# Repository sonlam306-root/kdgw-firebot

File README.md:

# kdgw-firebot — FireBot, robot chữa cháy chạy ray

FireBot là robot chữa cháy treo ngược dưới ray. Khi trạm gọi cháy phát hiện lửa, robot chạy tới vị trí, ngắm bằng camera nhiệt MLX90640 rồi phun nước qua tay 3 khớp. Trạm chính KD-GW vừa sạc pin vừa tiếp nước cho robot. Mọi nút điều khiển trong hệ đều dùng ESP.

| Hạng mục | Thông số |
|---|---|
| Ray | 2 tầng, nhôm dẹt 60×6 dựng đứng, dài 5 m hình chữ L, cua R600, mặt ray dưới cao 1,2 m so với sàn |
| Truyền động | Bánh xe chịu tải (vòng bi U626ZZ, trục M6 cấp 12.9); động cơ tuyến tính 12 V ở **cả 2 tầng ray**, chạy cùng pha (ADR-10) nên bình tự đẩy, robot không kéo bình; chia 9 module |
| Tốc độ | 1 m/s trên đoạn thẳng, 0,6 m/s khi vào cua |
| Phun | Tay 3 khớp, khớp 1 xoay 270° (DS3225 bản 270°): phun được **cả 2 bên ray**, bên nào có cháy thì phun bên đó (ADR-11) |
| Robot | Pin Li-ion 3S 12 V, bơm áp lực 12 V tầm phun 4–5 m, bình 3–4 L có cảm biến mực nước, phanh lò xo tự đóng khi mất điện |
| Điều khiển | KD-GW điều phối qua ESP-NOW và làm cầu sang MQTT; 2 trạm gọi cháy dùng ESP32-S3-CAM + cảm biến IR + nút nhấn |

## Thư mục

```
docs/                 bản vẽ tổng thể, catalog chi tiết in 3D, bản vẽ mạch in (PDF)
hardware/3d/          mô hình OpenSCAD tham số + STL (45 file) + ảnh render
hardware/pcb/FB-TRK/  board module ray ×9 (ESP32-C3, MAX3485, Hall, 2 driver DRV8313: ray dưới + ray trên)
hardware/pcb/FB-ROB/  board robot (ESP32-S3 DevKitC, 3 ngõ MOSFET, 4 servo, cảm biến)
firmware/             trk · rob · call · gw (chưa viết)
tools/                script sinh KiCad + autoroute (kigen), script vẽ PDF
```

## Tài liệu dự án
- SPEC (đã duyệt Checkpoint 1): https://claude.ai/artifact/Peooq6djiB6K9hsrVTQUn5
- PRODUCT (ADR-01…09): https://claude.ai/artifact/P67EzTibhUqXJA8hx2qiaA
- BOM dự toán: https://claude.ai/artifact/SVUP8KTw6aWDFcNGWLDG2Z (≈ 24,8 triệu đ, đã gồm 10 % dự phòng)

## Lắp đặt trạm gọi cháy
Mang đi triển lãm: dùng **khung định vị** (ADR-13, `hardware/3d/firebot_jig.scad`, STL ở `hardware/3d/stl_jig/`) — thanh sắt V lỗ bắt vào chân cột P2/P6, cột camera cắm đúng lỗ, chỉ hiệu chuẩn 1 lần ở nhà rồi chọn cấu hình trên dashboard.

Đo và dạy vị trí cho từng trạm theo `docs/Huong_dan_dat_tram_goi_chay.pdf` (ADR-12): dán thước số dọc ray, đo s_L, s_R bằng chân vuông góc, dạy trạm bằng ngọn nến, chạy thử không phun.

## Bước tiếp theo — thử nghiệm M0
1. Lắp 1 module ray + bogie dưới, đo lực đẩy (cần ≥ 5 N liên tục).
2. Thử bơm 12 V: đo tầm phun và lưu lượng.
3. Thử MLX90640 với bảng tra đạn đạo.

Board có chữ "Arden" ở mặt dưới.

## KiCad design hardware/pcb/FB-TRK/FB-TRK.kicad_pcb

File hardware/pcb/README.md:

# FireBot – mạch in (rev A, 2026-11-25)

| Board | Kích thước | SL | Gắn vào | File gửi xưởng |
|---|---|---|---|---|
| FB-TRK (module ray, 2 driver: ray dưới + ray trên) | 76 × 56 mm, 2 lớp | 9 (+1 dự phòng) | hộp `module_box`, 4 trụ M2.5 (64 × 44) | `FB-TRK/FB-TRK_gerber.zip` |
| FB-ROB (robot) | 84 × 84 mm, 2 lớp | 1 (+1 dự phòng) | khay `electronics_tray`, 4 trụ M3 (74 × 54) | `FB-ROB/FB-ROB_gerber.zip` |

- Mở bằng KiCad 7 trở lên: `*.kicad_pro`, sơ đồ `*.kicad_sch`, mạch `*.kicad_pcb`. Sơ đồ nối bằng nhãn net, chưa vẽ dây.
- Đặt hàng: FR4 1,6 mm. FB-ROB nên chọn đồng 2 oz vì đường bơm chịu ~5 A.
- Kiểm tra DRC: 0 lỗi, 0 chỗ chưa nối, ở cả hai board.
- Mỗi board có chữ "Arden" ở mặt dưới, góc phải. Không in tên board.
- Danh sách linh kiện: `*_bom.csv`. Toạ độ linh kiện cho SMT: `*_cpl.csv`.

**Kiểm tra trước khi hàn**
1. **ESP32-C3 SuperMini:** so chữ in trên PCB với chữ in trên module, vì vài lô xếp chân khác.
2. **ESP32-S3-DevKitC-1:** đo khoảng cách 2 hàng chân, bản vẽ dùng 22,86 mm.
3. **SimpleFOC Mini:** bản v1.0 và v1.1 xếp chân khác nhau, nên nối dây Dupont theo tên chân.

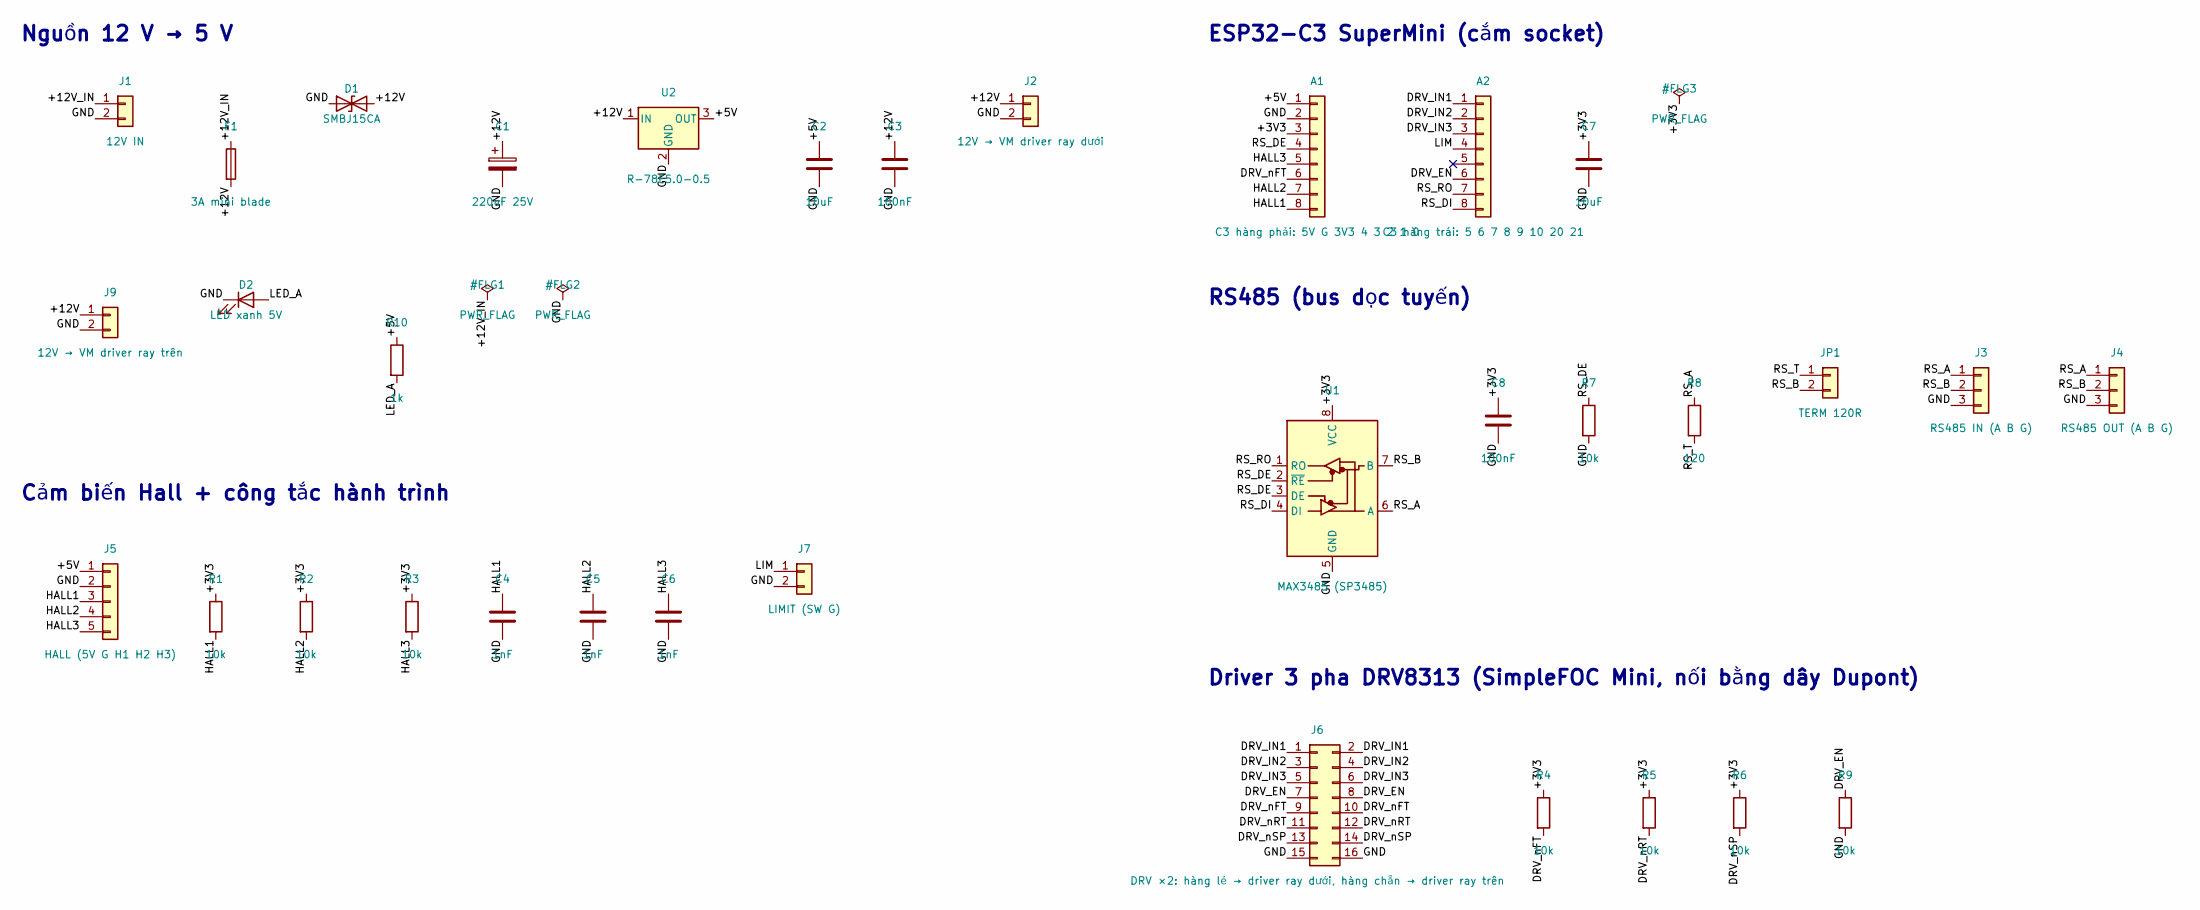
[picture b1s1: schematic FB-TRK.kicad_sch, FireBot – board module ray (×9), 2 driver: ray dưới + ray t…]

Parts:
A1: C3 hàng phải: 5V G 3V3 4 3 2 1 0; PinSocket_1x08_P2.54mm_Vertical
A2: C3 hàng trái: 5 6 7 8 9 10 20 21; PinSocket_1x08_P2.54mm_Vertical
C1: 220uF 25V; CP_Radial_D8.0mm_P3.50mm
C2, C7: 10uF; C_0805_2012Metric
C3, C8: 100nF; C_0805_2012Metric
C4, C5, C6: 1nF; C_0805_2012Metric
D1: SMBJ15CA; D_SMB
D2: LED xanh 5V; LED_0805_2012Metric
F1: 3A mini blade; Fuseholder_Blade_Mini_Keystone_3568
J1: 12V IN; TerminalBlock_Phoenix_MKDS-1,5-2-5.08_1x02_P5.08mm_Horizont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
J2: 12V → VM driver ray dưới; TerminalBlock_Phoenix_MKDS-1,5-2-5.08_1x02_P5.08mm_Horizont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
J3: RS485 IN (A B G); TerminalBlock_Phoenix_MKDS-1,5-3-5.08_1x03_P5.08mm_Horizont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
J4: RS485 OUT (A B G); TerminalBlock_Phoenix_MKDS-1,5-3-5.08_1x03_P5.08mm_Horizont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
J5: HALL (5V G H1 H2 H3); JST_XH_B5B-XH-A_1x05_P2.50mm_Vertical
J6: DRV ×2: hàng lẻ → driver ray dưới, hàng chẵn → dr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; PinHeader_2x08_P2.54mm_Vertical
J7: LIMIT (SW G); JST_XH_B2B-XH-A_1x02_P2.50mm_Vertical
J9: 12V → VM driver ray trên; TerminalBlock_Phoenix_MKDS-1,5-2-5.08_1x02_P5.08mm_Horizont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
JP1: TERM 120R; PinHeader_1x02_P2.54mm_Vertical
R1, R2, R3, R4, R5, R6, R7, R9: 10k; R_0805_2012Metric
R8: 120; R_0805_2012Metric
R10: 1k; R_0805_2012Metric
U1: MAX3485 (SP3485); SOIC-8_3.9x4.9mm_P1.27mm
U2: R-78E5.0-0.5; Converter_DCDC_RECOM_R-78E-0.5_THT

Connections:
+3V3: A1.3, C7.1, C8.1, R1.1, R2.1, R3.1, R4.1, R5.1, R6.1, U1.8 (VCC)
+5V: A1.1, C2.1, J5.1, R10.1, U2.3 (OUT)
+12V: C1.1, C3.1, D1.2 (A2), F1.2, J2.1, J9.1, U2.1 (IN)
+12V_IN: F1.1, J1.1
DRV_EN: A2.6, J6.7, J6.8, R9.1
DRV_IN1: A2.1, J6.1, J6.2
DRV_IN2: A2.2, J6.3, J6.4
DRV_IN3: A2.3, J6.5, J6.6
DRV_nFT: A1.6, J6.9, J6.10, R4.2
DRV_nRT: J6.11, J6.12, R5.2
DRV_nSP: J6.13, J6.14, R6.2
GND: A1.2, C1.2, C2.2, C3.2, C4.2, C5.2, C6.2, C7.2, C8.2, D1.1 (A1), D2.1 (K), J1.2, J2.2, J3.3, J4.3, J5.2, J6.15, J6.16, J7.2, J9.2, R7.2, R9.2, U1.5 (GND), U2.2 (GND)
HALL1: A1.8, C4.1, J5.3, R1.2
HALL2: A1.7, C5.1, J5.4, R2.2
HALL3: A1.5, C6.1, J5.5, R3.2
LED_A: D2.2 (A), R10.2
LIM: A2.4, J7.1
RS_A: J3.1, J4.1, R8.1, U1.6 (A)
RS_B: J3.2, J4.2, JP1.2, U1.7 (B)
RS_DE: A1.4, R7.1, U1.2 (~RE), U1.3 (DE)
RS_DI: A2.8, U1.4 (DI)
RS_RO: A2.7, U1.1 (RO)
RS_T: JP1.1, R8.2

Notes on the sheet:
Nguồn 12 V → 5 V
ESP32-C3 SuperMini (cắm socket)
RS485 (bus dọc tuyến)
Cảm biến Hall + công tắc hành trình
Driver 3 pha DRV8313 (SimpleFOC Mini, nối bằng dây Dupont)

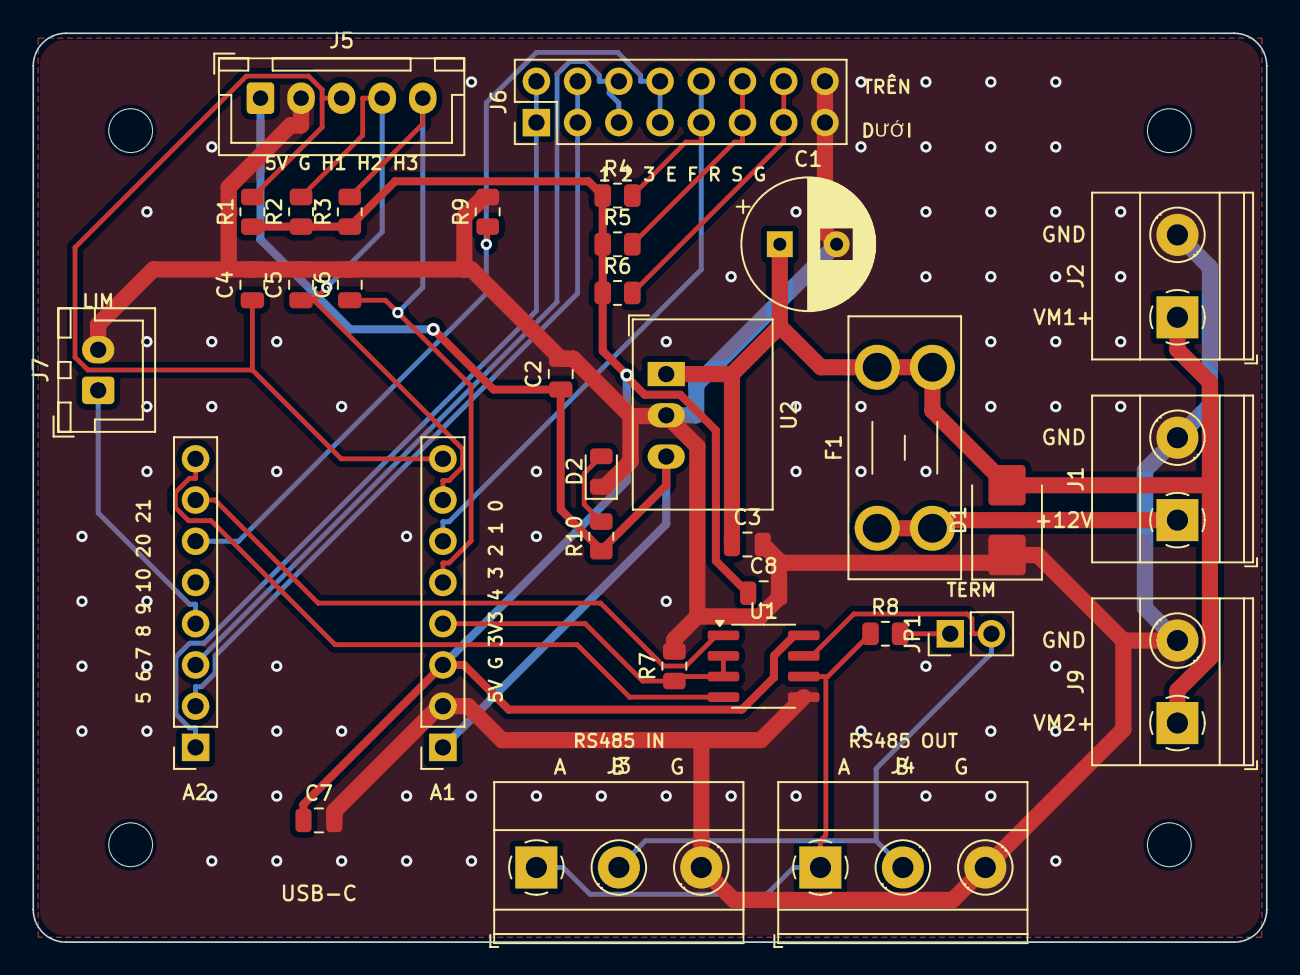
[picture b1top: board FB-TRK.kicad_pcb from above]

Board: 2 copper layers, 76.0 x 56.0 mm, 38 parts (0 on the bottom side), 23 nets.

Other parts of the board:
H1, H2, H3, H4: MountingHole_2.7mm_M2.5

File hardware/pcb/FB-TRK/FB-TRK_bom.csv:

Ref,Giá trị,Footprint,SL
A1,C3 hàng phải: 5V G 3V3 4 3 2 1 0,PinSocket_1x08_P2.54mm_Vertical,1
A2,C3 hàng trái: 5 6 7 8 9 10 20 21,PinSocket_1x08_P2.54mm_Vertical,1
C1,220uF 25V,CP_Radial_D8.0mm_P3.50mm,1
C2 C7,10uF,C_0805_2012Metric,2
C3 C8,100nF,C_0805_2012Metric,2
C4 C5 C6,1nF,C_0805_2012Metric,3
D1,SMBJ15CA,D_SMB,1
D2,LED xanh 5V,LED_0805_2012Metric,1
F1,3A mini blade,Fuseholder_Blade_Mini_Keystone_3568,1
J1,12V IN,"TerminalBlock_Phoenix_MKDS-1,5-2-5.08_1x02_P5.08mm_Horizontal",1
J2,12V → VM driver ray dưới,"TerminalBlock_Phoenix_MKDS-1,5-2-5.08_1x02_P5.08mm_Horizontal",1
J3,RS485 IN (A B G),"TerminalBlock_Phoenix_MKDS-1,5-3-5.08_1x03_P5.08mm_Horizontal",1
J4,RS485 OUT (A B G),"TerminalBlock_Phoenix_MKDS-1,5-3-5.08_1x03_P5.08mm_Horizontal",1
J5,HALL (5V G H1 H2 H3),JST_XH_B5B-XH-A_1x05_P2.50mm_Vertical,1
J6,"DRV ×2: hàng lẻ → driver ray dưới, hàng chẵn → driver ray trên",PinHeader_2x08_P2.54mm_Vertical,1
J7,LIMIT (SW G),JST_XH_B2B-XH-A_1x02_P2.50mm_Vertical,1
J9,12V → VM driver ray trên,"TerminalBlock_Phoenix_MKDS-1,5-2-5.08_1x02_P5.08mm_Horizontal",1
JP1,TERM 120R,PinHeader_1x02_P2.54mm_Vertical,1
R1 R2 R3 R4 R5 R6 R7 R9,10k,R_0805_2012Metric,8
R8,120,R_0805_2012Metric,1
R10,1k,R_0805_2012Metric,1
U1,MAX3485 (SP3485),SOIC-8_3.9x4.9mm_P1.27mm,1
U2,R-78E5.0-0.5,Converter_DCDC_RECOM_R-78E-0.5_THT,1

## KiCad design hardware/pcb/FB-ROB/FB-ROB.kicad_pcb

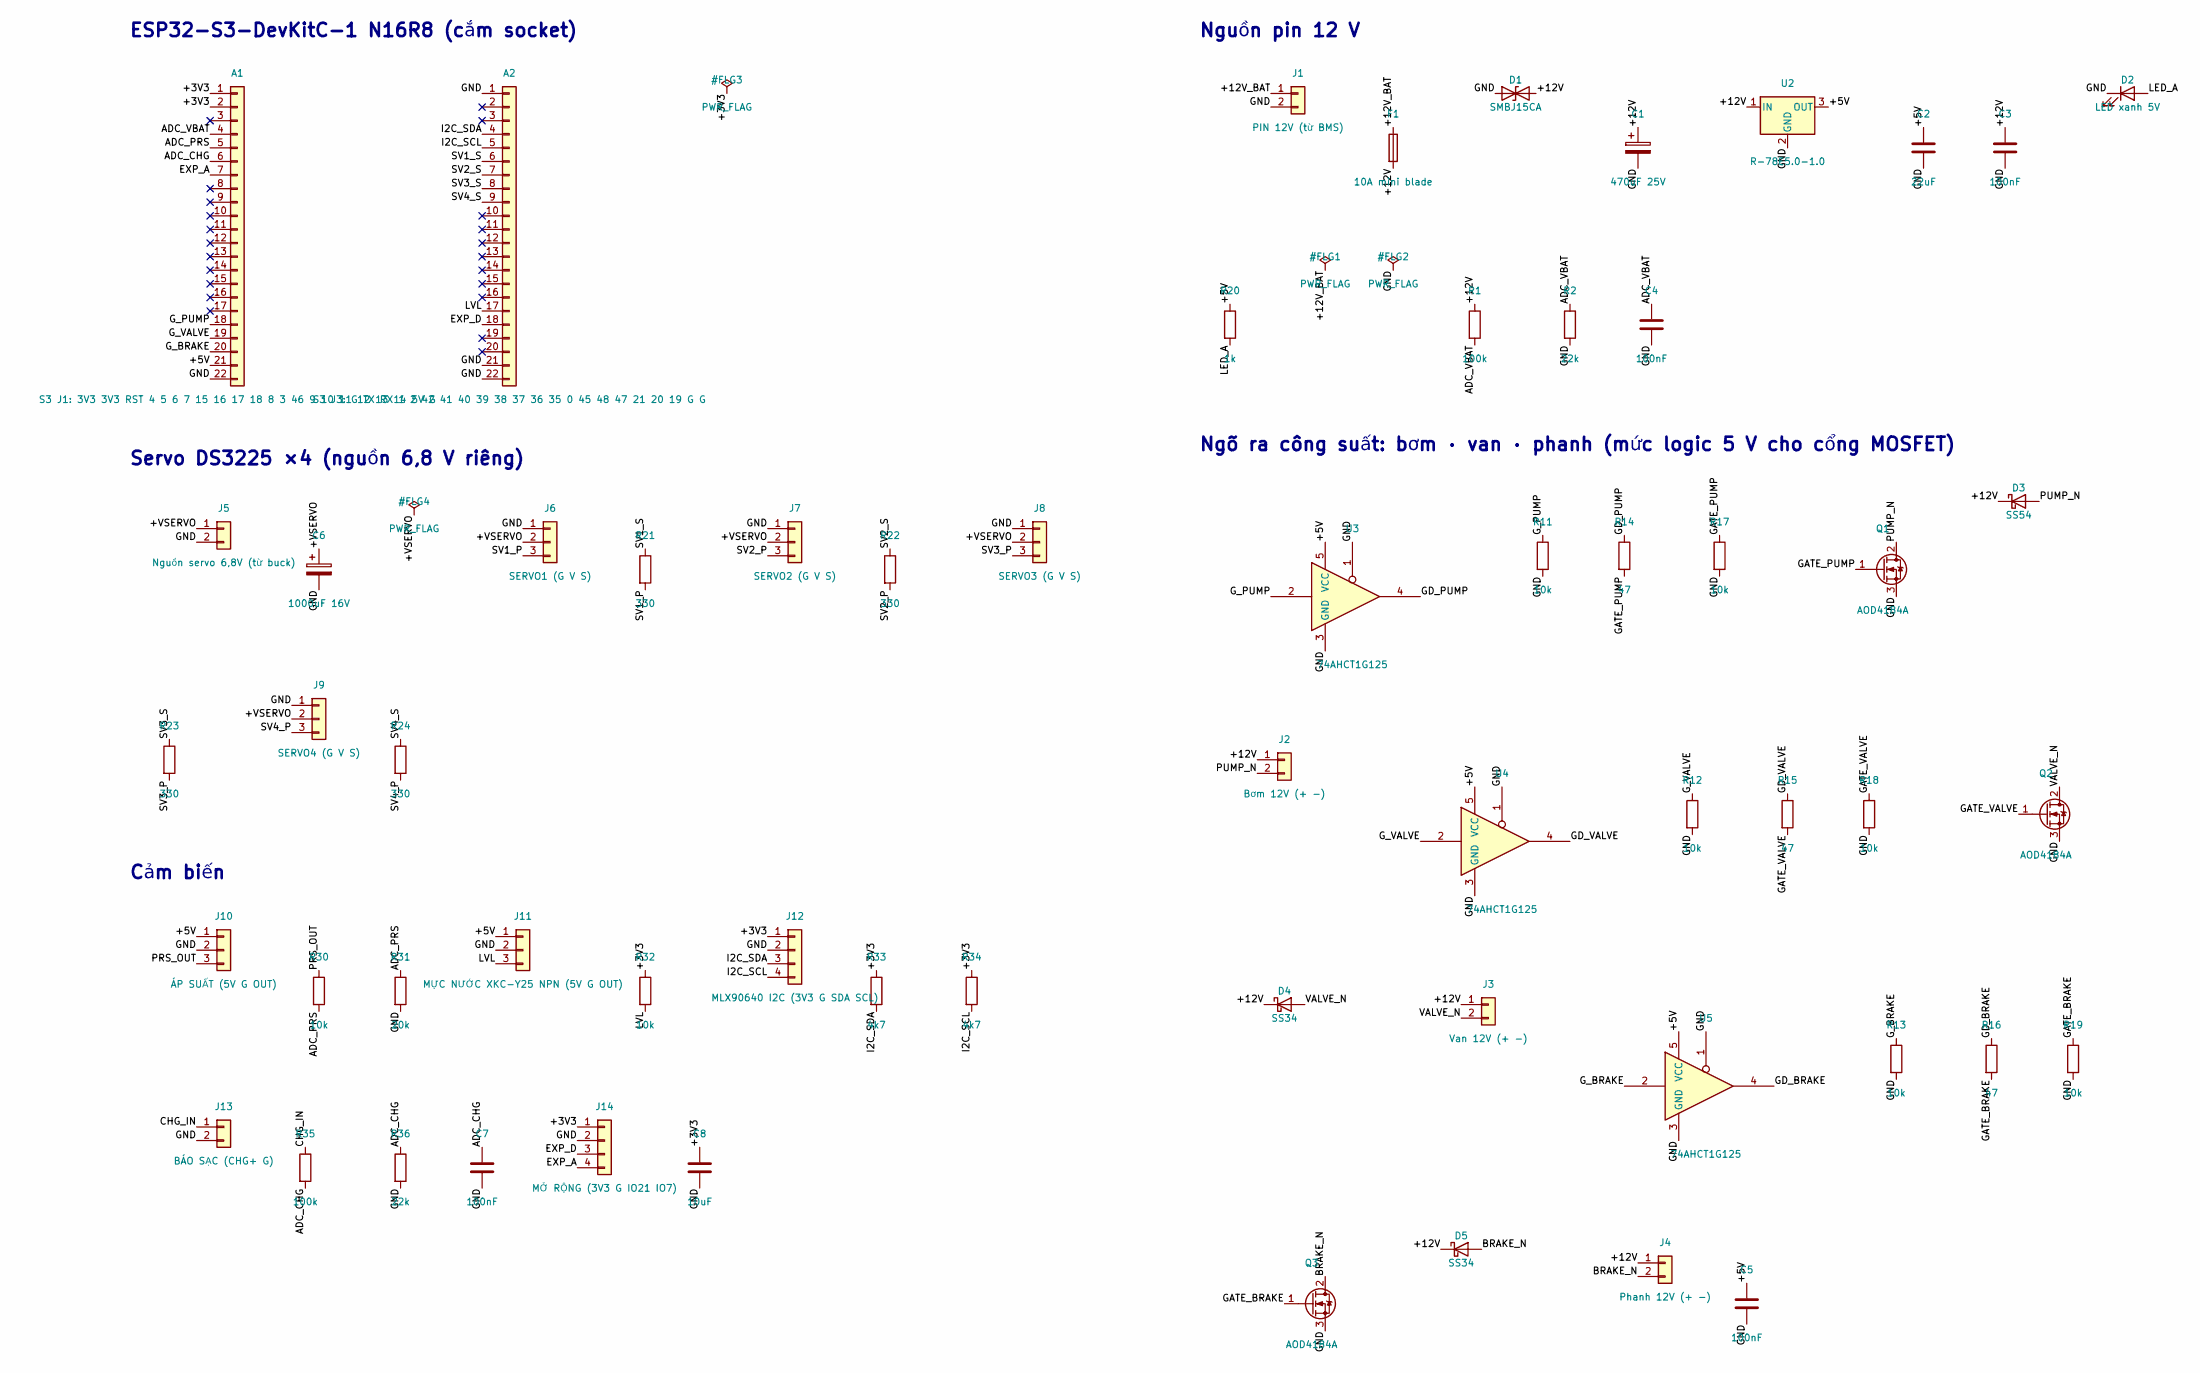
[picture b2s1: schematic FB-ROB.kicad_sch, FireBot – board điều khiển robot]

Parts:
A1: S3 J1: 3V3 3V3 RST 4 5 6 7 15 16 17 18 8 3 46 9 1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; PinSocket_1x22_P2.54mm_Vertical
A2: S3 J3: G TX RX 1 2 42 41 40 39 38 37 36 35 0 45 4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; PinSocket_1x22_P2.54mm_Vertical
C1: 470uF 25V; CP_Radial_D10.0mm_P5.00mm
C2: 22uF; C_0805_2012Metric
C3, C4, C5, C7: 100nF; C_0805_2012Metric
C6: 1000uF 16V; CP_Radial_D10.0mm_P5.00mm
C8: 10uF; C_0805_2012Metric
D1: SMBJ15CA; D_SMB
D2: LED xanh 5V; LED_0805_2012Metric
D3: SS54; D_SMB
D4, D5: SS34; D_SMA
F1: 10A mini blade; Fuseholder_Blade_Mini_Keystone_3568
J1: PIN 12V (từ BMS); TerminalBlock_Phoenix_MKDS-1,5-2-5.08_1x02_P5.08mm_Horizont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
J2: Bơm 12V (+ −); TerminalBlock_Phoenix_MKDS-1,5-2-5.08_1x02_P5.08mm_Horizont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
J3: Van 12V (+ −); TerminalBlock_Phoenix_MKDS-1,5-2-5.08_1x02_P5.08mm_Horizont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
J4: Phanh 12V (+ −); TerminalBlock_Phoenix_MKDS-1,5-2-5.08_1x02_P5.08mm_Horizont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
J5: Nguồn servo 6,8V (từ buck); TerminalBlock_Phoenix_MKDS-1,5-2-5.08_1x02_P5.08mm_Horizont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
J6: SERVO1 (G V S); PinHeader_1x03_P2.54mm_Vertical
J7: SERVO2 (G V S); PinHeader_1x03_P2.54mm_Vertical
J8: SERVO3 (G V S); PinHeader_1x03_P2.54mm_Vertical
J9: SERVO4 (G V S); PinHeader_1x03_P2.54mm_Vertical
J10: ÁP SUẤT (5V G OUT); JST_XH_B3B-XH-A_1x03_P2.50mm_Vertical
J11: MỰC NƯỚC XKC-Y25 NPN (5V G OUT); JST_XH_B3B-XH-A_1x03_P2.50mm_Vertical
J12: MLX90640 I2C (3V3 G SDA SCL); JST_XH_B4B-XH-A_1x04_P2.50mm_Vertical
J13: BÁO SẠC (CHG+ G); JST_XH_B2B-XH-A_1x02_P2.50mm_Vertical
J14: MỞ RỘNG (3V3 G IO21 IO7); JST_XH_B4B-XH-A_1x04_P2.50mm_Vertical
Q1, Q2, Q3: AOD4184A; TO-252-2
R1, R35: 100k; R_0805_2012Metric
R2, R36: 22k; R_0805_2012Metric
R11, R12, R13, R17, R18, R19, R30, R32: 10k; R_0805_2012Metric
R14, R15, R16: 47; R_0805_2012Metric
R20: 1k; R_0805_2012Metric
R21, R22, R23, R24: 330; R_0805_2012Metric
R31: 20k; R_0805_2012Metric
R33, R34: 4k7; R_0805_2012Metric
U2: R-78E5.0-1.0; Converter_DCDC_RECOM_R-78E-0.5_THT
U3, U4, U5: 74AHCT1G125; SOT-23-5

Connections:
+3V3: A1.1, A1.2, C8.1, J12.1, J14.1, R32.1, R33.1, R34.1
+5V: A1.21, C2.1, C5.1, J10.1, J11.1, R20.1, U2.3 (OUT), U3.5 (VCC), U4.5 (VCC), U5.5 (VCC)
+12V: C1.1, C3.1, D1.2 (A2), D3.1 (K), D4.1 (K), D5.1 (K), F1.2, J2.1, J3.1, J4.1, R1.1, U2.1 (IN)
+12V_BAT: F1.1, J1.1
+VSERVO: C6.1, J5.1, J6.2, J7.2, J8.2, J9.2
ADC_CHG: A1.6, C7.1, R35.2, R36.1
ADC_PRS: A1.5, R30.2, R31.1
ADC_VBAT: A1.4, C4.1, R1.2, R2.1
BRAKE_N: D5.2 (A), J4.2, Q3.2 (D)
CHG_IN: J13.1, R35.1
EXP_A: A1.7, J14.4
EXP_D: A2.18, J14.3
GATE_BRAKE: Q3.1 (G), R16.2, R19.1
GATE_PUMP: Q1.1 (G), R14.2, R17.1
GATE_VALVE: Q2.1 (G), R15.2, R18.1
GD_BRAKE: R16.1, U5.4
GD_PUMP: R14.1, U3.4
GD_VALVE: R15.1, U4.4
GND: A1.22, A2.1, A2.21, A2.22, C1.2, C2.2, C3.2, C4.2, C5.2, C6.2, C7.2, C8.2, D1.1 (A1), D2.1 (K), J1.2, J5.2, J6.1, J7.1, J8.1, J9.1, J10.2, J11.2, J12.2, J13.2, J14.2, Q1.3 (S), Q2.3 (S), Q3.3 (S), R2.2, R11.2, R12.2, R13.2, R17.2, R18.2, R19.2, R31.2, R36.2, U2.2 (GND), U3.1, U3.3 (GND), U4.1, U4.3 (GND), U5.1, U5.3 (GND)
G_BRAKE: A1.20, R13.1, U5.2
G_PUMP: A1.18, R11.1, U3.2
G_VALVE: A1.19, R12.1, U4.2
I2C_SCL: A2.5, J12.4, R34.2
I2C_SDA: A2.4, J12.3, R33.2
LED_A: D2.2 (A), R20.2
LVL: A2.17, J11.3, R32.2
PRS_OUT: J10.3, R30.1
PUMP_N: D3.2 (A), J2.2, Q1.2 (D)
SV1_P: J6.3, R21.2
SV1_S: A2.6, R21.1
SV2_P: J7.3, R22.2
SV2_S: A2.7, R22.1
SV3_P: J8.3, R23.2
SV3_S: A2.8, R23.1
SV4_P: J9.3, R24.2
SV4_S: A2.9, R24.1
VALVE_N: D4.2 (A), J3.2, Q2.2 (D)

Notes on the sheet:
ESP32-S3-DevKitC-1 N16R8 (cắm socket)
Nguồn pin 12 V
Ngõ ra công suất: bơm · van · phanh (mức logic 5 V cho cổng MOSFET)
Servo DS3225 ×4 (nguồn 6,8 V riêng)
Cảm biến

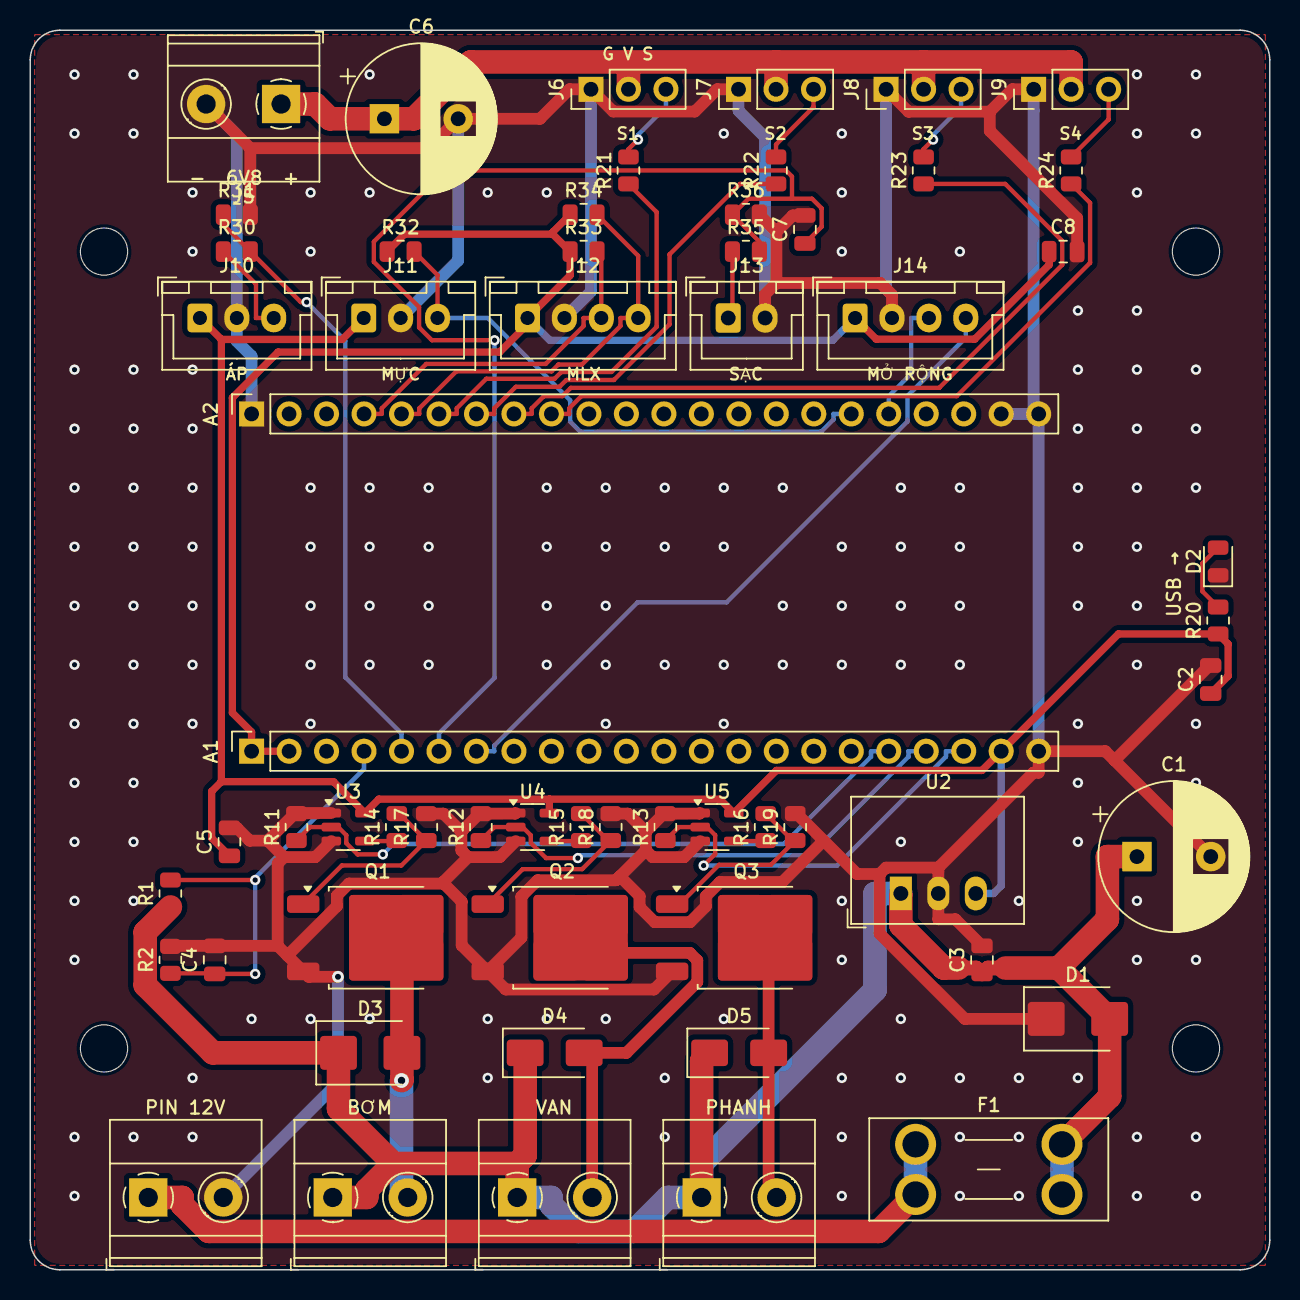
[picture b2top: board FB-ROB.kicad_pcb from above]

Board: 2 copper layers, 84.0 x 84.0 mm, 64 parts (0 on the bottom side), 37 nets.

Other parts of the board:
H1, H2, H3, H4: MountingHole_3.2mm_M3

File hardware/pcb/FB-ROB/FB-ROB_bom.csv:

Ref,Giá trị,Footprint,SL
A1,S3 J1: 3V3 3V3 RST 4 5 6 7 15 16 17 18 8 3 46 9 10 11 12 13 14 5V G,PinSocket_1x22_P2.54mm_Vertical,1
A2,S3 J3: G TX RX 1 2 42 41 40 39 38 37 36 35 0 45 48 47 21 20 19 G G,PinSocket_1x22_P2.54mm_Vertical,1
C1,470uF 25V,CP_Radial_D10.0mm_P5.00mm,1
C2,22uF,C_0805_2012Metric,1
C3 C4 C5 C7,100nF,C_0805_2012Metric,4
C6,1000uF 16V,CP_Radial_D10.0mm_P5.00mm,1
C8,10uF,C_0805_2012Metric,1
D1,SMBJ15CA,D_SMB,1
D2,LED xanh 5V,LED_0805_2012Metric,1
D3,SS54,D_SMB,1
D4 D5,SS34,D_SMA,2
F1,10A mini blade,Fuseholder_Blade_Mini_Keystone_3568,1
J1,PIN 12V (từ BMS),"TerminalBlock_Phoenix_MKDS-1,5-2-5.08_1x02_P5.08mm_Horizontal",1
J2,Bơm 12V (+ −),"TerminalBlock_Phoenix_MKDS-1,5-2-5.08_1x02_P5.08mm_Horizontal",1
J3,Van 12V (+ −),"TerminalBlock_Phoenix_MKDS-1,5-2-5.08_1x02_P5.08mm_Horizontal",1
J4,Phanh 12V (+ −),"TerminalBlock_Phoenix_MKDS-1,5-2-5.08_1x02_P5.08mm_Horizontal",1
J5,"Nguồn servo 6,8V (từ buck)","TerminalBlock_Phoenix_MKDS-1,5-2-5.08_1x02_P5.08mm_Horizontal",1
J6,SERVO1 (G V S),PinHeader_1x03_P2.54mm_Vertical,1
J7,SERVO2 (G V S),PinHeader_1x03_P2.54mm_Vertical,1
J8,SERVO3 (G V S),PinHeader_1x03_P2.54mm_Vertical,1
J9,SERVO4 (G V S),PinHeader_1x03_P2.54mm_Vertical,1
J10,ÁP SUẤT (5V G OUT),JST_XH_B3B-XH-A_1x03_P2.50mm_Vertical,1
J11,MỰC NƯỚC XKC-Y25 NPN (5V G OUT),JST_XH_B3B-XH-A_1x03_P2.50mm_Vertical,1
J12,MLX90640 I2C (3V3 G SDA SCL),JST_XH_B4B-XH-A_1x04_P2.50mm_Vertical,1
J13,BÁO SẠC (CHG+ G),JST_XH_B2B-XH-A_1x02_P2.50mm_Vertical,1
J14,MỞ RỘNG (3V3 G IO21 IO7),JST_XH_B4B-XH-A_1x04_P2.50mm_Vertical,1
Q1 Q2 Q3,AOD4184A,TO-252-2,3
R1 R35,100k,R_0805_2012Metric,2
R2 R36,22k,R_0805_2012Metric,2
R11 R12 R13 R17 R18 R19 R30 R32,10k,R_0805_2012Metric,8
R14 R15 R16,47,R_0805_2012Metric,3
R20,1k,R_0805_2012Metric,1
R21 R22 R23 R24,330,R_0805_2012Metric,4
R31,20k,R_0805_2012Metric,1
R33 R34,4k7,R_0805_2012Metric,2
U2,R-78E5.0-1.0,Converter_DCDC_RECOM_R-78E-0.5_THT,1
U3 U4 U5,74AHCT1G125,SOT-23-5,3

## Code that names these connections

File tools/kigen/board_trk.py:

"""FB-TRK: track module board (x9). ESP32-C3 SuperMini + MAX3485 + R-78E 5V,
Hall inputs, header to a DRV8313 (SimpleFOC Mini) driver, limit switch."""
R0805 = "Resistor_SMD:R_0805_2012Metric"
C0805 = "Capacitor_SMD:C_0805_2012Metric"
SOCK8 = "Connector_PinSocket_2.54mm:PinSocket_1x08_P2.54mm_Vertical"
TB2 = "TerminalBlock_Phoenix:TerminalBlock_Phoenix_MKDS-1,5-2-5.08_1x02_P5.08mm_Horizontal"
TB3 = "TerminalBlock_Phoenix:TerminalBlock_Phoenix_MKDS-1,5-3-5.08_1x03_P5.08mm_Horizontal"
XH = lambda n: f"Connector_JST:JST_XH_B{n}B-XH-A_1x0{n}_P2.50mm_Vertical"


def R(ref, val, a, b, at, blk, note=None):
    return dict(ref=ref, sym="Device:R", val=val, fp=R0805, pins={"1": a, "2": b}, at=at, blk=blk, note=note)


def C(ref, val, a, b, at, blk):
    return dict(ref=ref, sym="Device:C", val=val, fp=C0805, pins={"1": a, "2": b}, at=at, blk=blk)


P = "Nguồn 12 V → 5 V"
M = "ESP32-C3 SuperMini (cắm socket)"
RS = "RS485 (bus dọc tuyến)"
H = "Cảm biến Hall + công tắc hành trình"
D = "Driver 3 pha DRV8313 (SimpleFOC Mini, nối bằng dây Dupont)"

parts = [
    # ---- power
    dict(ref="J1", sym="Connector_Generic:Conn_01x02", val="12V IN", fp=TB2, pins={"1": "+12V_IN", "2": "GND"}, at=(70.5, 30.0, 90), blk=P),
    dict(ref="F1", sym="Device:Fuse", val="3A mini blade", fp="Fuse:Fuseholder_Blade_Mini_Keystone_3568", pins={"1": "+12V_IN", "2": "+12V"}, at=(52.0, 30.5, 90), blk=P),
    dict(ref="D1", sym="Device:D_TVS", val="SMBJ15CA", fp="Diode_SMD:D_SMB", pins={"1": "GND", "2": "+12V"}, at=(60.0, 30.0, 90), blk=P),
    dict(ref="C1", sym="Device:C_Polarized", val="220uF 25V", fp="Capacitor_THT:CP_Radial_D8.0mm_P3.50mm", pins={"1": "+12V", "2": "GND"}, at=(46.0, 13.0, 0), blk=P),
    dict(ref="U2", sym="Regulator_Switching:R-78E5.0-0.5", val="R-78E5.0-0.5", fp="Converter_DCDC:Converter_DCDC_RECOM_R-78E-0.5_THT", pins={"1": "+12V", "2": "GND", "3": "+5V"}, at=(39.0, 21.0, 270), blk=P),
    C("C2", "10uF", "+5V", "GND", (32.5, 21.0, 90), P),
    C("C3", "100nF", "+12V", "GND", (44.0, 31.5, 0), P),
    dict(ref="J2", sym="Connector_Generic:Conn_01x02", val="12V → VM driver ray dưới", fp=TB2, pins={"1": "+12V", "2": "GND"}, at=(70.5, 17.5, 90), blk=P),
    dict(ref="J9", sym="Connector_Generic:Conn_01x02", val="12V → VM driver ray trên", fp=TB2, pins={"1": "+12V", "2": "GND"}, at=(70.5, 42.5, 90), blk=P),
    dict(ref="D2", sym="Device:LED", val="LED xanh 5V", fp="LED_SMD:LED_0805_2012Metric", pins={"1": "GND", "2": "LED_A"}, at=(35.0, 27.0, 90), blk=P),
    R("R10", "1k", "+5V", "LED_A", (35.0, 31.0, 90), P),
    dict(ref="#FLG1", sym="power:PWR_FLAG", val="PWR_FLAG", pins={"1": "+12V_IN"}, blk=P, nobom=True),
    dict(ref="#FLG2", sym="power:PWR_FLAG", val="PWR_FLAG", pins={"1": "GND"}, blk=P, nobom=True),
    # ---- MCU (two 1x8 sockets; USB-C toward the bottom edge)
    dict(ref="A1", sym="Connector_Generic:Conn_01x08", val="C3 hàng phải: 5V G 3V3 4 3 2 1 0", fp=SOCK8,
         pins={"1": "+5V", "2": "GND", "3": "+3V3", "4": "RS_DE", "5": "HALL3", "6": "DRV_nFT", "7": "HALL2", "8": "HALL1"},
         at=(25.24, 44.0, 180), blk=M),
    dict(ref="A2", sym="Connector_Generic:Conn_01x08", val="C3 hàng trái: 5 6 7 8 9 10 20 21", fp=SOCK8,
         pins={"1": "DRV_IN1", "2": "DRV_IN2", "3": "DRV_IN3", "4": "LIM", "6": "DRV_EN", "7": "RS_RO", "8": "RS_DI"},
         at=(10.0, 44.0, 180), blk=M),
    C("C7", "10uF", "+3V3", "GND", (17.6, 48.5, 0), M),
    dict(ref="#FLG3", sym="power:PWR_FLAG", val="PWR_FLAG", pins={"1": "+3V3"}, blk=M, nobom=True),
    # ---- RS485
    dict(ref="U1", sym="Interface_UART:MAX3485", val="MAX3485 (SP3485)", fp="Package_SO:SOIC-8_3.9x4.9mm_P1.27mm",
         pins={"1": "RS_RO", "2": "RS_DE", "3": "RS_DE", "4": "RS_DI", "5": "GND", "6": "RS_A", "7": "RS_B", "8": "+3V3"},
         at=(45.0, 39.0, 0), blk=RS),
    C("C8", "100nF", "+3V3", "GND", (45.0, 34.5, 0), RS),
    R("R7", "10k", "RS_DE", "GND", (39.5, 39.0, 90), RS, "DE/RE kéo xuống: mặc định nhận"),
    R("R8", "120", "RS_A", "RS_T", (52.5, 37.0, 0), RS, "điện trở cuối tuyến"),
    dict(ref="JP1", sym="Connector_Generic:Conn_01x02", val="TERM 120R", fp="Connector_PinHeader_2.54mm:PinHeader_1x02_P2.54mm_Vertical",
         pins={"1": "RS_T", "2": "RS_B"}, at=(56.5, 37.0, 90), blk=RS, note="cắm jumper ở module M0 và M8"),
    dict(ref="J3", sym="Connector_Generic:Conn_01x03", val="RS485 IN (A B G)", fp=TB3, pins={"1": "RS_A", "2": "RS_B", "3": "GND"}, at=(31.0, 51.4, 0), blk=RS),
    dict(ref="J4", sym="Connector_Generic:Conn_01x03", val="RS485 OUT (A B G)", fp=TB3, pins={"1": "RS_A", "2": "RS_B", "3": "GND"}, at=(48.5, 51.4, 0), blk=RS),
    # ---- Hall + limit
    dict(ref="J5", sym="Connector_Generic:Conn_01x05", val="HALL (5V G H1 H2 H3)", fp=XH(5),
         pins={"1": "+5V", "2": "GND", "3": "HALL1", "4": "HALL2", "5": "HALL3"}, at=(14.0, 4.0, 0), blk=H),
    R("R1", "10k", "+3V3", "HALL1", (13.5, 11.0, 90), H),
    R("R2", "10k", "+3V3", "HALL2", (16.5, 11.0, 90), H),
    R("R3", "10k", "+3V3", "HALL3", (19.5, 11.0, 90), H),
    C("C4", "1nF", "HALL1", "GND", (13.5, 15.5, 90), H),
    C("C5", "1nF", "HALL2", "GND", (16.5, 15.5, 90), H),
    C("C6", "1nF", "HALL3", "GND", (19.5, 15.5, 90), H),
    dict(ref="J7", sym="Connector_Generic:Conn_01x02", val="LIMIT (SW G)", fp=XH(2), pins={"1": "LIM", "2": "GND"}, at=(4.0, 22.0, 90), blk=H),
    # ---- driver header
    dict(ref="J6", sym="Connector_Generic:Conn_02x08_Odd_Even", val="DRV ×2: hàng lẻ → driver ray dưới, hàng chẵn → driver ray trên", fp="Connector_PinHeader_2.54mm:PinHeader_2x08_P2.54mm_Vertical",
         pins={'1': 'DRV_IN1', '2': 'DRV_IN1', '3': 'DRV_IN2', '4': 'DRV_IN2', '5': 'DRV_IN3', '6': 'DRV_IN3', '7': 'DRV_EN', '8': 'DRV_EN', '9': 'DRV_nFT', '10': 'DRV_nFT', '11': 'DRV_nRT', '12': 'DRV_nRT', '13': 'DRV_nSP', '14': 'DRV_nSP', '15': 'GND', '16': 'GND'},
         at=(31.0, 5.5, 90), blk=D, note="2 driver chạy song song cùng tín hiệu: cuộn ray trên cùng pha với ray dưới (ADR-10)"),
    R("R4", "10k", "+3V3", "DRV_nFT", (36.0, 10.0, 0), D),
    R("R5", "10k", "+3V3", "DRV_nRT", (36.0, 13.0, 0), D),
    R("R6", "10k", "+3V3", "DRV_nSP", (36.0, 16.0, 0), D),
    R("R9", "10k", "DRV_EN", "GND", (28.0, 11.0, 90), D, "EN kéo xuống: driver tắt khi khởi động"),
]

B = dict(
    name="FB-TRK", title="FireBot – board module ray (×9), 2 driver: ray dưới + ray trên", date="2026-11-25", rev="A",
    comment="ESP32-C3 SuperMini · MAX3485 · R-78E5.0 · 3 Hall · DRV8313",
    parts=parts, w=76.0, h=56.0, ox=100.0, oy=100.0, corner=2.0,
    holes=[(6, 6), (70, 6), (6, 50), (70, 50)], hole_fp="MountingHole_2.7mm_M2.5",
    netclasses=[("Power", (1.0, 0.2, 1.0, 0.5), ["+12V_IN", "+12V", "GND"]), ("P5", (0.5, 0.2, 0.8, 0.4), ["+5V", "+3V3"])],
    texts=[
        ("Arden", 66, 53.5, 0, "B.SilkS", 1.5),
        ("+12V", 63.5, 30.0, 0, "F.SilkS", 0.9), ("GND", 63.5, 24.9, 0, "F.SilkS", 0.9),
        ("VM1+", 63.5, 17.5, 0, "F.SilkS", 0.9), ("GND", 63.5, 12.4, 0, "F.SilkS", 0.9), ("VM2+", 63.5, 42.5, 0, "F.SilkS", 0.9), ("GND", 63.5, 37.4, 0, "F.SilkS", 0.9),
        ("A    B    G", 36.1, 45.2, 0, "F.SilkS", 0.9), ("A    B    G", 53.6, 45.2, 0, "F.SilkS", 0.9), ("RS485 IN", 36.1, 43.6, 0, "F.SilkS", 0.8), ("RS485 OUT", 53.6, 43.6, 0, "F.SilkS", 0.8),
        ("5V G H1 H2 H3", 19.0, 8.0, 0, "F.SilkS", 0.8),
        ("1 2 3 E F R S G", 40.0, 8.7, 0, "F.SilkS", 0.8), ("DƯỚI", 52.6, 6.0, 0, "F.SilkS", 0.8), ("TRÊN", 52.6, 3.3, 0, "F.SilkS", 0.8),
        ("USB-C", 17.6, 53.0, 0, "F.SilkS", 0.9),
        ("5V G 3V3 4 3 2 1 0", 28.5, 35.0, 90, "F.SilkS", 0.8),
        ("5 6 7 8 9 10 20 21", 6.8, 35.0, 90, "F.SilkS", 0.8),
        ("LIM", 4.0, 16.5, 0, "F.SilkS", 0.8), ("TERM", 57.8, 34.3, 0, "F.SilkS", 0.8),
    ],
)

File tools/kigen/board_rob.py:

"""FB-ROB: robot main board. ESP32-S3-DevKitC-1 (N16R8) on sockets, 3 low-side
MOSFET outputs (pump / valve / brake) with 5 V gate drive, 4 servo ports, sensors."""
R0805 = "Resistor_SMD:R_0805_2012Metric"
C0805 = "Capacitor_SMD:C_0805_2012Metric"
SOCK22 = "Connector_PinSocket_2.54mm:PinSocket_1x22_P2.54mm_Vertical"
TB2 = "TerminalBlock_Phoenix:TerminalBlock_Phoenix_MKDS-1,5-2-5.08_1x02_P5.08mm_Horizontal"
XH = lambda n: f"Connector_JST:JST_XH_B{n}B-XH-A_1x0{n}_P2.50mm_Vertical"
HDR3 = "Connector_PinHeader_2.54mm:PinHeader_1x03_P2.54mm_Vertical"


def R(ref, val, a, b, at, blk, note=None):
    return dict(ref=ref, sym="Device:R", val=val, fp=R0805, pins={"1": a, "2": b}, at=at, blk=blk, note=note)


def C(ref, val, a, b, at, blk):
    return dict(ref=ref, sym="Device:C", val=val, fp=C0805, pins={"1": a, "2": b}, at=at, blk=blk)


P = "Nguồn pin 12 V"
M = "ESP32-S3-DevKitC-1 N16R8 (cắm socket)"
O = "Ngõ ra công suất: bơm · van · phanh (mức logic 5 V cho cổng MOSFET)"
S = "Servo DS3225 ×4 (nguồn 6,8 V riêng)"
X = "Cảm biến"

# DevKitC-1 headers (USB toward +X). J1 row at y=48.86, J3 row at y=26.0, pin 1 at x=15
J1 = {1: "+3V3", 2: "+3V3", 4: "ADC_VBAT", 5: "ADC_PRS", 6: "ADC_CHG", 7: "EXP_A", 18: "G_PUMP", 19: "G_VALVE", 20: "G_BRAKE", 21: "+5V", 22: "GND"}
J3 = {1: "GND", 4: "I2C_SDA", 5: "I2C_SCL", 6: "SV1_S", 7: "SV2_S", 8: "SV3_S", 9: "SV4_S", 17: "LVL", 18: "EXP_D", 21: "GND", 22: "GND"}

parts = [
    dict(ref="A1", sym="Connector_Generic:Conn_01x22", val="S3 J1: 3V3 3V3 RST 4 5 6 7 15 16 17 18 8 3 46 9 10 11 12 13 14 5V G", fp=SOCK22,
         pins={str(k): v for k, v in J1.items()}, at=(15.0, 48.86, 90), blk=M),
    dict(ref="A2", sym="Connector_Generic:Conn_01x22", val="S3 J3: G TX RX 1 2 42 41 40 39 38 37 36 35 0 45 48 47 21 20 19 G G", fp=SOCK22,
         pins={str(k): v for k, v in J3.items()}, at=(15.0, 26.0, 90), blk=M),
    dict(ref="#FLG3", sym="power:PWR_FLAG", val="PWR_FLAG", pins={"1": "+3V3"}, blk=M, nobom=True),
    # ---- power
    dict(ref="J1", sym="Connector_Generic:Conn_01x02", val="PIN 12V (từ BMS)", fp=TB2, pins={"1": "+12V_BAT", "2": "GND"}, at=(8.0, 79.1, 0), blk=P, hideref=True),
    dict(ref="F1", sym="Device:Fuse", val="10A mini blade", fp="Fuse:Fuseholder_Blade_Mini_Keystone_3568", pins={"1": "+12V_BAT", "2": "+12V"}, at=(60.0, 75.5, 0), blk=P),
    dict(ref="D1", sym="Device:D_TVS", val="SMBJ15CA", fp="Diode_SMD:D_SMB", pins={"1": "GND", "2": "+12V"}, at=(71.0, 67.0, 0), blk=P),
    dict(ref="C1", sym="Device:C_Polarized", val="470uF 25V", fp="Capacitor_THT:CP_Radial_D10.0mm_P5.00mm", pins={"1": "+12V", "2": "GND"}, at=(75.0, 56.0, 0), blk=P),
    dict(ref="U2", sym="Regulator_Switching:R-78E5.0-1.0", val="R-78E5.0-1.0", fp="Converter_DCDC:Converter_DCDC_RECOM_R-78E-0.5_THT", pins={"1": "+12V", "2": "GND", "3": "+5V"}, at=(59.0, 58.5, 0), blk=P),
    C("C2", "22uF", "+5V", "GND", (80.0, 44.0, 90), P),
    C("C3", "100nF", "+12V", "GND", (64.5, 63.0, 90), P),
    dict(ref="D2", sym="Device:LED", val="LED xanh 5V", fp="LED_SMD:LED_0805_2012Metric", pins={"1": "GND", "2": "LED_A"}, at=(80.5, 36.0, 90), blk=P),
    R("R20", "1k", "+5V", "LED_A", (80.5, 40.0, 90), P),
    dict(ref="#FLG1", sym="power:PWR_FLAG", val="PWR_FLAG", pins={"1": "+12V_BAT"}, blk=P, nobom=True),
    dict(ref="#FLG2", sym="power:PWR_FLAG", val="PWR_FLAG", pins={"1": "GND"}, blk=P, nobom=True),
    R("R1", "100k", "+12V", "ADC_VBAT", (9.5, 58.5, 90), P, "chia áp đo pin 12,6 V → 2,27 V"),
    R("R2", "22k", "ADC_VBAT", "GND", (9.5, 63.0, 90), P),
    C("C4", "100nF", "ADC_VBAT", "GND", (12.5, 63.0, 90), P),
]

# ---- 3 low-side outputs
outs = [("PUMP", "Bơm 12V", 20.5, "SS54", "Diode_SMD:D_SMB", "G_PUMP"),
        ("VALVE", "Van 12V", 33.0, "SS34", "Diode_SMD:D_SMA", "G_VALVE"),
        ("BRAKE", "Phanh 12V", 45.5, "SS34", "Diode_SMD:D_SMA", "G_BRAKE")]
for i, (n, lbl, xt, dio, dfp, g) in enumerate(outs, start=1):
    xc = xt + 2.54
    parts += [
        dict(ref=f"U{2+i}", sym="74xGxx:74AHCT1G125", val="74AHCT1G125", fp="Package_TO_SOT_SMD:SOT-23-5",
             pins={"1": "GND", "2": g, "3": "GND", "4": f"GD_{n}", "5": "+5V"}, at=(xc - 1.5, 54.0, 0), blk=O),
        R(f"R{10+i}", "10k", g, "GND", (xc - 5.0, 54.0, 90), O, "kéo xuống: tắt khi ESP khởi động"),
        R(f"R{13+i}", "47", f"GD_{n}", f"GATE_{n}", (xc + 1.8, 54.0, 90), O),
        R(f"R{16+i}", "10k", f"GATE_{n}", "GND", (xc + 3.8, 54.0, 90), O),
        dict(ref=f"Q{i}", sym="Device:Q_NMOS_GDS", val="AOD4184A", fp="Package_TO_SOT_SMD:TO-252-2",
             pins={"1": f"GATE_{n}", "2": f"{n}_N", "3": "GND"}, at=(xc + 0.5, 61.5, 0), blk=O),
        dict(ref=f"D{2+i}", sym="Device:D_Schottky", val=dio, fp=dfp, pins={"1": "+12V", "2": f"{n}_N"}, at=(xc, 69.3, 0), blk=O),
        dict(ref=f"J{1+i}", sym="Connector_Generic:Conn_01x02", val=f"{lbl} (+ −)", fp=TB2, pins={"1": "+12V", "2": f"{n}_N"}, at=(xt, 79.1, 0), blk=O, hideref=True),
    ]
parts.append(C("C5", "100nF", "+5V", "GND", (13.5, 55.0, 90), O))

# ---- servos
parts += [
    dict(ref="J5", sym="Connector_Generic:Conn_01x02", val="Nguồn servo 6,8V (từ buck)", fp=TB2, pins={"1": "+VSERVO", "2": "GND"}, at=(17.0, 5.0, 180), blk=S),
    dict(ref="C6", sym="Device:C_Polarized", val="1000uF 16V", fp="Capacitor_THT:CP_Radial_D10.0mm_P5.00mm", pins={"1": "+VSERVO", "2": "GND"}, at=(24.0, 6.0, 0), blk=S),
    dict(ref="#FLG4", sym="power:PWR_FLAG", val="PWR_FLAG", pins={"1": "+VSERVO"}, blk=S, nobom=True),
]
for i in range(1, 5):
    x = 38.0 + (i - 1) * 10.0
    parts += [
        dict(ref=f"J{5+i}", sym="Connector_Generic:Conn_01x03", val=f"SERVO{i} (G V S)", fp=HDR3, pins={"1": "GND", "2": "+VSERVO", "3": f"SV{i}_P"}, at=(x, 4.0, 90), blk=S),
        R(f"R{20+i}", "330", f"SV{i}_S", f"SV{i}_P", (x + 2.54, 9.5, 90), S),
    ]

# ---- sensors
parts += [
    dict(ref="J10", sym="Connector_Generic:Conn_01x03", val="ÁP SUẤT (5V G OUT)", fp=XH(3), pins={"1": "+5V", "2": "GND", "3": "PRS_OUT"}, at=(11.5, 19.5, 0), blk=X),
    R("R30", "10k", "PRS_OUT", "ADC_PRS", (14.0, 15.0, 0), X, "0,5–4,5 V → 0,33–3,0 V"),
    R("R31", "20k", "ADC_PRS", "GND", (14.0, 12.5, 0), X),
    dict(ref="J11", sym="Connector_Generic:Conn_01x03", val="MỰC NƯỚC XKC-Y25 NPN (5V G OUT)", fp=XH(3), pins={"1": "+5V", "2": "GND", "3": "LVL"}, at=(22.6, 19.5, 0), blk=X),
    R("R32", "10k", "+3V3", "LVL", (25.1, 15.0, 0), X),
    dict(ref="J12", sym="Connector_Generic:Conn_01x04", val="MLX90640 I2C (3V3 G SDA SCL)", fp=XH(4), pins={"1": "+3V3", "2": "GND", "3": "I2C_SDA", "4": "I2C_SCL"}, at=(33.7, 19.5, 0), blk=X),
    R("R33", "4k7", "+3V3", "I2C_SDA", (37.5, 15.0, 0), X),
    R("R34", "4k7", "+3V3", "I2C_SCL", (37.5, 12.5, 0), X),
    dict(ref="J13", sym="Connector_Generic:Conn_01x02", val="BÁO SẠC (CHG+ G)", fp=XH(2), pins={"1": "CHG_IN", "2": "GND"}, at=(47.3, 19.5, 0), blk=X),
    R("R35", "100k", "CHG_IN", "ADC_CHG", (48.5, 15.0, 0), X),
    R("R36", "22k", "ADC_CHG", "GND", (48.5, 12.5, 0), X),
    C("C7", "100nF", "ADC_CHG", "GND", (52.5, 13.5, 90), X),
    dict(ref="J14", sym="Connector_Generic:Conn_01x04", val="MỞ RỘNG (3V3 G IO21 IO7)", fp=XH(4), pins={"1": "+3V3", "2": "GND", "3": "EXP_D", "4": "EXP_A"}, at=(55.9, 19.5, 0), blk=X),
    C("C8", "10uF", "+3V3", "GND", (70.0, 15.0, 0), X),
]

B = dict(
    name="FB-ROB", title="FireBot – board điều khiển robot", date="2026-11-25", rev="A",
    comment="ESP32-S3-DevKitC-1 · 3 MOSFET · 4 servo · MLX90640 · áp suất · mực nước",
    parts=parts, w=84.0, h=84.0, ox=100.0, oy=100.0, corner=2.0,
    holes=[(5, 15), (79, 15), (5, 69), (79, 69)], hole_fp="MountingHole_3.2mm_M3",
    netclasses=[("Big", (1.6, 0.2, 1.0, 0.5), ["+12V_BAT", "+12V", "PUMP_N", "+VSERVO"]),
                ("Mid", (0.8, 0.2, 0.8, 0.4), ["VALVE_N", "BRAKE_N", "GND"]),
                ("P5", (0.5, 0.2, 0.8, 0.4), ["+5V", "+3V3"])],
    texts=[
        ("Arden", 78.0, 81.5, 0, "B.SilkS", 1.5),
        ("PIN 12V", 10.5, 73.0, 0, "F.SilkS", 0.9),
        ("BƠM", 23.0, 73.0, 0, "F.SilkS", 0.9), ("VAN", 35.5, 73.0, 0, "F.SilkS", 0.9), ("PHANH", 48.0, 73.0, 0, "F.SilkS", 0.9),
        ("−  6V8  +", 14.5, 10.0, 0, "F.SilkS", 0.9),
        ("G V S", 40.5, 1.6, 0, "F.SilkS", 0.8), ("S1", 40.5, 7.0, 0, "F.SilkS", 0.8), ("S2", 50.5, 7.0, 0, "F.SilkS", 0.8),
        ("S3", 60.5, 7.0, 0, "F.SilkS", 0.8), ("S4", 70.5, 7.0, 0, "F.SilkS", 0.8),
        ("ÁP", 14.0, 23.3, 0, "F.SilkS", 0.8), ("MỰC", 25.1, 23.3, 0, "F.SilkS", 0.8), ("MLX", 37.5, 23.3, 0, "F.SilkS", 0.8),
        ("SẠC", 48.5, 23.3, 0, "F.SilkS", 0.8), ("MỞ RỘNG", 59.6, 23.3, 0, "F.SilkS", 0.8),
        ("USB →", 77.5, 37.5, 90, "F.SilkS", 0.9),
    ],
)
